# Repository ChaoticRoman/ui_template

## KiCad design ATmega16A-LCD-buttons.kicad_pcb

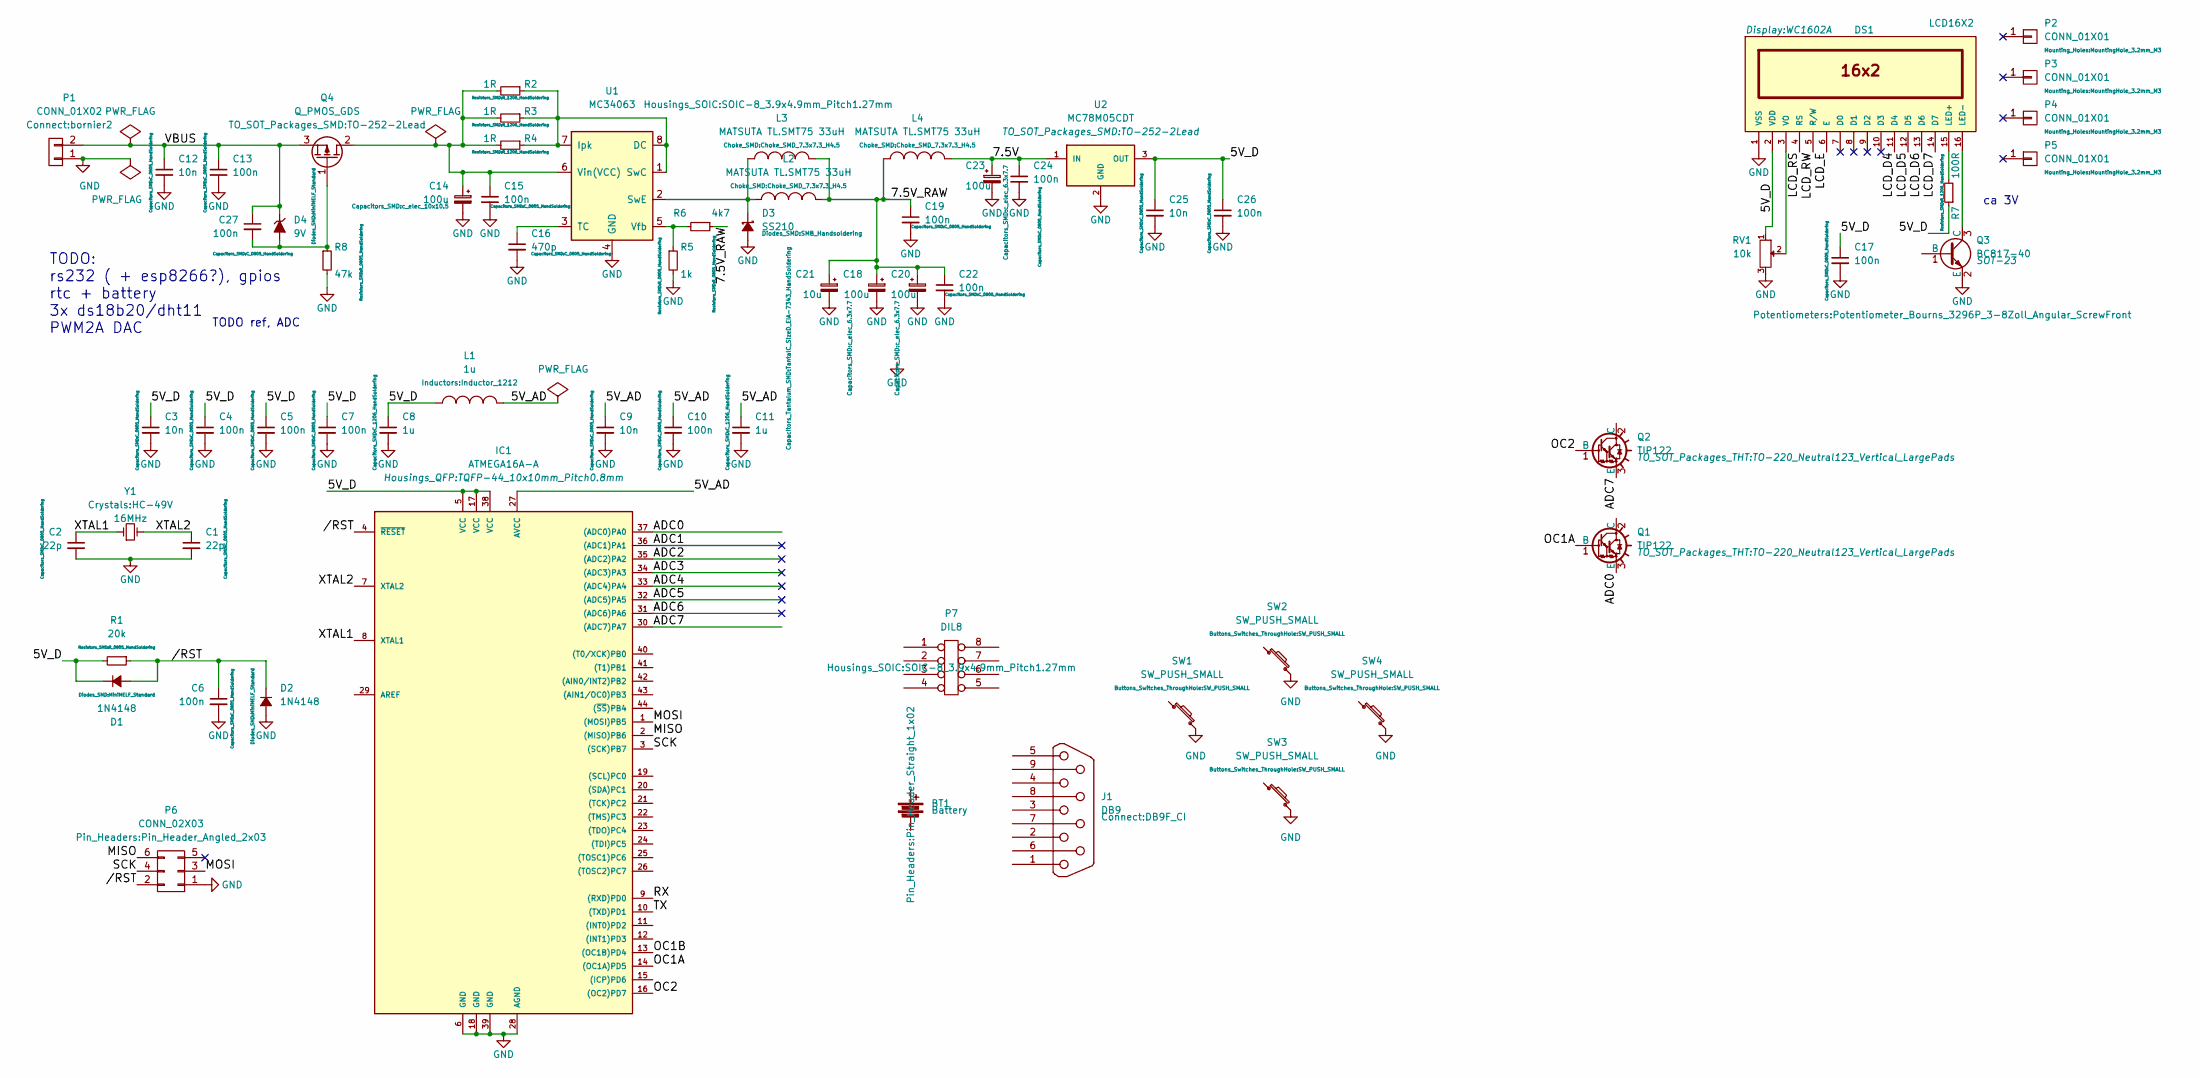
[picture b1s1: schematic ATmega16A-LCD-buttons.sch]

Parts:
BT1: Battery; Pin_Header_Straight_1x02
C1, C2: 22p; C_0805_HandSoldering
C3, C9, C12, C25: 10n; C_0805_HandSoldering
C4, C5, C6, C7, C10, C13, C15, C17, C19, C22, C24, C26, C27: 100n; C_0805_HandSoldering
C8, C11: 1u; C_1206_HandSoldering
C14: 100u; c_elec_10x10.5
C16: 470p; C_0805_HandSoldering
C18, C20, C23: 100u; c_elec_6.3x7.7
C21: 10u; TantalC_SizeD_EIA-7343_HandSoldering
D1, D2: 1N4148; MiniMELF_Standard
D3: SS210; SMB_Handsoldering
D4: 9V; MiniMELF_Standard
DS1: LCD16X2; WC1602A
IC1: ATMEGA16A-A; TQFP-44_10x10mm_Pitch0.8mm
J1: DB9; DB9F_CI
L1: 1u; Inductor_1212
L2, L3, L4: MATSUTA TL.SMT75 33uH; Choke_SMD_7.3x7.3_H4.5
P1: CONN_01X02; bornier2
P2, P3, P4, P5: CONN_01X01; MountingHole_3.2mm_M3
P6: CONN_02X03; Pin_Header_Angled_2x03
P7: DIL8; SOIC-8_3.9x4.9mm_Pitch1.27mm
Q1, Q2: TIP122; TO-220_Neutral123_Vertical_LargePads
Q3: BC817-40; SOT-23
Q4: Q_PMOS_GDS; TO-252-2Lead
R1: 20k; R_0805_HandSoldering
R2, R3, R4: 1R; R_1206_HandSoldering
R5: 1k; R_0805_HandSoldering
R6: 4k7; R_0805_HandSoldering
R7: 100R; R_1206_HandSoldering
R8: 47k; R_0805_HandSoldering
RV1: 10k; Potentiometer_Bourns_3296P_3-8Zoll_Angular_ScrewFront
SW1, SW2, SW3, SW4: SW_PUSH_SMALL
U1: MC34063; SOIC-8_3.9x4.9mm_Pitch1.27mm
U2: MC78M05CDT; TO-252-2Lead
Y1: 16MHz; HC-49V

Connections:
/5V_AD: C9.1, C10.1, C11.1, IC1.27 (AVCC), L1.2
/5V_D: C3.1, C4.1, C5.1, C7.1, C8.1, C17.1, C25.1, C26.1, D1.1 (K), DS1.2 (VDD), IC1.5 (VCC), IC1.17 (VCC), IC1.38 (VCC), L1.1, R1.2, R7.1, RV1.1, U2.3 (OUT)
/7.5V: C23.1, C24.1, L4.2, U2.1 (IN)
/7.5V_RAW: C18.1, C19.1, C20.1, C21.1, C22.1, L2.2, L3.2, L4.1, R6.1
//RST: C6.1, D1.2 (A), D2.1 (K), IC1.4 (~RESET), P6.2, R1.1
/ADC0: IC1.37 ((ADC0)PA0), Q1.3 (E)
/ADC1: IC1.36 ((ADC1)PA1)
/ADC2: IC1.35 ((ADC2)PA2)
/ADC3: IC1.34 ((ADC3)PA3)
/ADC4: IC1.33 ((ADC4)PA4)
/ADC5: IC1.32 ((ADC5)PA5)
/ADC6: IC1.31 ((ADC6)PA6)
/ADC7: IC1.30 ((ADC7)PA7), Q2.3 (E)
/LCD_D4: DS1.11 (D4)
/LCD_D5: DS1.12 (D5)
/LCD_D6: DS1.13 (D6)
/LCD_D7: DS1.14 (D7)
/LCD_E: DS1.6 (E)
/LCD_RS: DS1.4 (RS)
/LCD_RW: DS1.5 (R/W)
/MISO: IC1.2 ((MISO)PB6), P6.6
/MOSI: IC1.1 ((MOSI)PB5), P6.3
/OC1A: IC1.14 ((OC1A)PD5), Q1.1 (B)
/OC1B: IC1.13 ((OC1B)PD4)
/OC2: IC1.16 ((OC2)PD7), Q2.1 (B)
/RX: IC1.9 ((RXD)PD0)
/SCK: IC1.3 ((SCK)PB7), P6.4
/TX: IC1.10 ((TXD)PD1)
/VBUS: C12.1, C13.1, C27.1, D4.1 (K), P1.2, Q4.3 (S)
/XTAL1: C2.1, IC1.8 (XTAL1), Y1.1
/XTAL2: C1.1, IC1.7 (XTAL2), Y1.2
GND: C1.2, C2.2, C3.2, C4.2, C5.2, C6.2, C7.2, C8.2, C9.2, C10.2, C11.2, C12.2, C13.2, C14.2, C15.2, C16.2, C17.2, C18.2, C19.2, C20.2, C21.2, C22.2, C23.2, C24.2, C25.2, C26.2, D2.2 (A), D3.2 (A), DS1.1 (VSS), IC1.6 (GND), IC1.18 (GND), IC1.28 (AGND), IC1.39 (GND), P1.1, P6.1, Q3.2 (E), R5.2, R8.2, RV1.3, SW1.2, SW2.2, SW3.2, SW4.2, U1.4 (GND), U2.2 (GND)
unnamed: C14.1, C15.1, Q4.2 (D), R2.2, R3.2, R4.2, U1.6 (Vin(VCC))
unnamed: C16.1, U1.3 (TC)
unnamed: C27.2, D4.2 (A), Q4.1 (G), R8.1
unnamed: D3.1 (K), L2.1, L3.1, U1.2 (SwE)
unnamed: DS1.3 (VO), RV1.2
unnamed: DS1.15 (LED+), R7.2
unnamed: DS1.16 (LED-), Q3.3 (C)
unnamed: R2.1, R3.1, R4.1, U1.1 (SwC), U1.7 (Ipk), U1.8 (DC)
unnamed: R5.1, R6.2, U1.5 (Vfb)

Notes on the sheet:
TODO: rs232 ( + esp8266?), gpios rtc + battery 3x ds18b20/dht11 PWM2A DAC
TODO ref, ADC
ca 3V

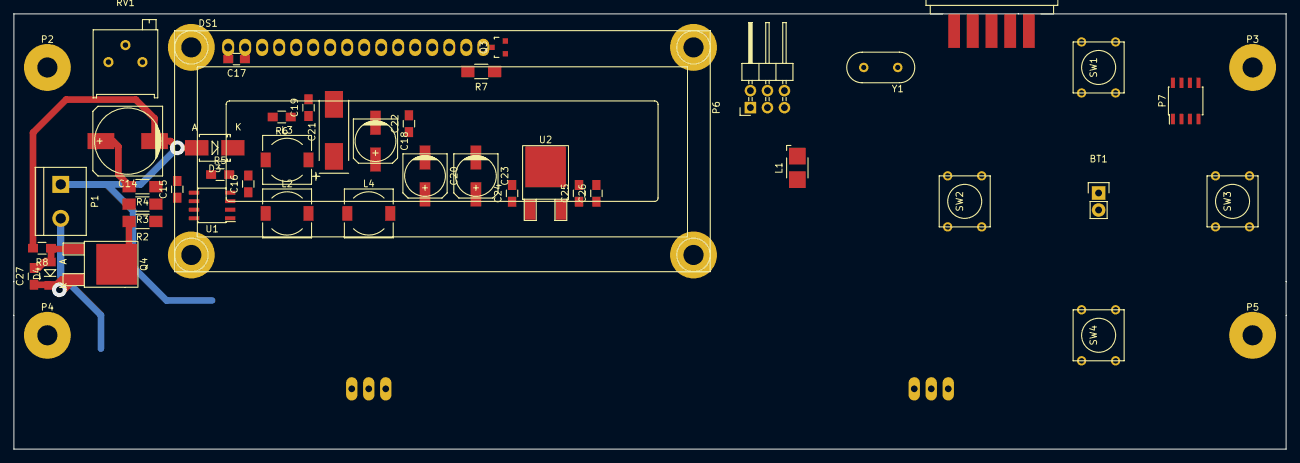
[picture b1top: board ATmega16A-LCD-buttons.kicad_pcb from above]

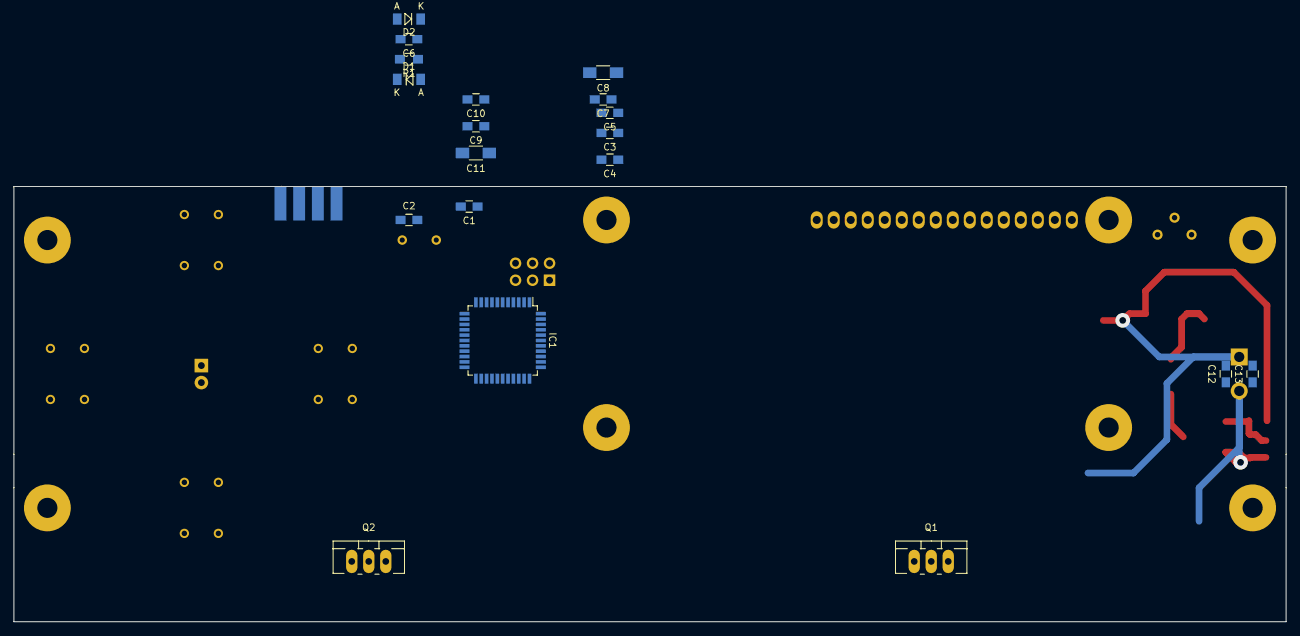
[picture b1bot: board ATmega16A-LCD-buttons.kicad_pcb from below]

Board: 2 copper layers, 190.0 x 65.0 mm, 66 parts (19 on the bottom side), 25 nets.

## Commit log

2025-11-27 Add license
